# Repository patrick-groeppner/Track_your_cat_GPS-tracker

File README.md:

# Track_your_cat_GPS-tracker
project files for the development of a gps tracker for the offline movement tracking of your beloved home cat. Can also be used for other tracking purposes like car movement recordings or the measurement of walking routs

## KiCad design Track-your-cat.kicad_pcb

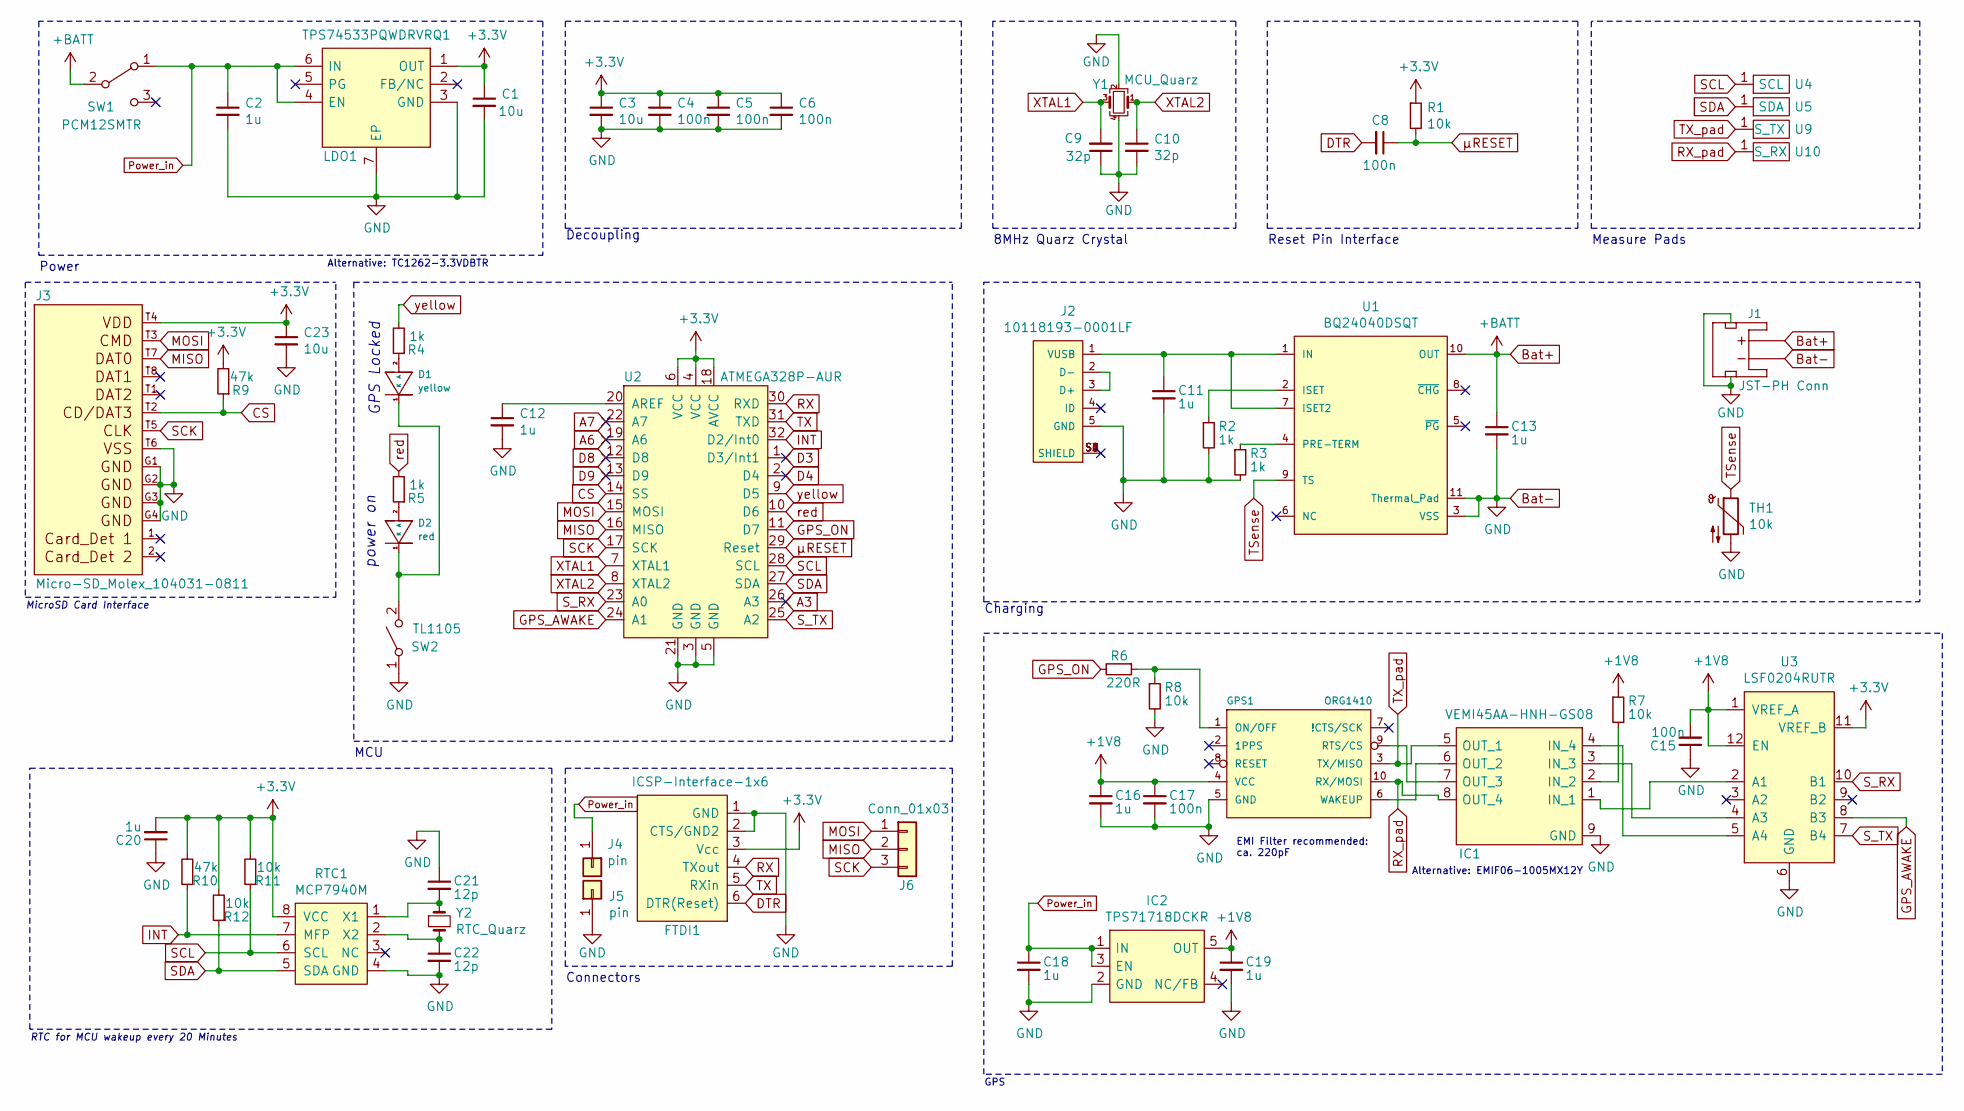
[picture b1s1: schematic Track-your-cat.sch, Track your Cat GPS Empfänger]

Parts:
C1, C3, C23: 10u; C_0805_2012Metric_Pad1.18x1.45mm_HandSolder
C2, C11, C12, C13, C16, C18, C19, C20: 1u; C_0603_1608Metric_Pad1.08x0.95mm_HandSolder
C4, C5, C6, C8, C15, C17: 100n; C_0603_1608Metric_Pad1.08x0.95mm_HandSolder
C9, C10: 32p; C_0603_1608Metric_Pad1.08x0.95mm_HandSolder
C21, C22: 12p; C_0603_1608Metric_Pad1.08x0.95mm_HandSolder
D1: yellow; LED_3MM
D2: red; LED_3MM
FTDI1: ICSP-Interface-1x6; ICSP1; Mouser Part Number ---
GPS1: ORG1410; Mouser Part Number ---
IC1: VEMI45AA-HNH-GS08; Manufacturer_Part_Number VEMI45AA-HNH-GS08; Mouser Part Number 78-VEMI45AA-HNH
IC2: TPS71718DCKR; SC70; Manufacturer_Part_Number TPS71718DCKR; Mouser Part Number 595-TPS71718DCKR
J1: JST_2MM_MALE; JST-2-SMD; Mouser Part Number adafruit 1769
J2: 10118193-0001LF; FCI_10118193-0001LF
J3: Micro-SD_Molex_104031-0811; Micro-SD-Card-Molex_104031-0811; current rating 0.5A; voltage rating 10V; Mouser Part Number 538-104031-0811; digikey description CONN MICRO SD CARD PUSH-PULL R/A
J4, J5: pin; PinHeader_1x01_P2.54mm_Vertical
J6: Conn_01x03; PinHeader_1x03_P2.54mm_Vertical
LDO1: TPS74533PQWDRVRQ1; Manufacturer_Part_Number TPS74533PQWDRVRQ1; Mouser Part Number 595-PS74533PQWDRVRQ1
R1, R7, R8, R11, R12: 10k; R_0603_1608Metric_Pad0.98x0.95mm_HandSolder
R2, R3, R4, R5: 1k; R_0603_1608Metric_Pad0.98x0.95mm_HandSolder
R6: 220R; R_0603_1608Metric_Pad0.98x0.95mm_HandSolder
R9, R10: 47k; R_0603_1608Metric_Pad0.98x0.95mm_HandSolder
RTC1: MCP7940M; SOIC-8_W3.9mm; Mouser Part Nbr. 579-MCP7940MT-I/SN
SW1: PCM12SMTR; Mouser Part Number CUS-13TB PCM12SMTR
SW2: TL1105; TL1105VF250Q
TH1: 10k; THERM_NXRT15XH103FA1B040; Mouser Part Nbr. NXFT15XH103FA2B050
U1: BQ24040DSQT; Texas_Instruments-DSQ0010A-0-0-IPC_C; output voltage 4.2V; Mouser Part Number 595-BQ24040DSQT; digikey description IC BATT CHG LI-ION 1 CELL 10SON
U2: ATMEGA328P-AUR; TQFP-32_7x7mm; MPN ATMEGA328P-AUR; Digi-Key_PN ATMEGA328P-AURCT-ND
U3: LSF0204RUTR; IC_LSF0204RUTR; PARTREV 4210580/C 06/12
U4: SCL; Single0805pad
U5: SDA; Single0805pad
U9: S_TX; Single0805pad
U10: S_RX; Single0805pad
Y1: MCU_Quarz; Crystal_SMD_3225-4Pin_3.2x2.5mm_HandSoldering; Mouser Part Number ABM8AIG-8.000MHZ-1Z-T
Y2: RTC_Quarz; XTAL_ECS-.327-12.5-34QN-TR; Mouser Part Nbr. 732-MC30632.7680KA0R

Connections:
+1V8: C15.2, C16.1, C17.1, C19.1, GPS1.4 (VCC), IC2.5 (OUT), R7.1, U3.1 (VREF_A), U3.12 (EN)
+3V3: C1.1, C3.1, C4.1, C5.1, C6.1, C20.2, C23.1, FTDI1.3 (Vcc), J3.T4, LDO1.1 (OUT), R1.1, R9.2, R10.2, R11.2, R12.2, RTC1.8 (VCC), U2.4 (VCC), U2.6 (VCC), U2.18 (AVCC), U3.11 (VREF_B)
A3: U2.26 (A3)
A6: U2.19 (A6)
A7: U2.22 (A7)
Bat+: C13.1, J1.2 (+), SW1.2 (B), U1.10 (OUT)
Bat-: C1.2, C2.2, C3.2, C4.2, C5.2, C6.2, C9.1, C10.2, C11.2, C12.2, C13.2, C15.1, C16.2, C17.2, C18.2, C19.2, C20.1, C21.1, C22.2, C23.2, FTDI1.1 (GND), FTDI1.2 (CTS/GND2), GPS1.5 (GND), IC1.9 (GND), IC2.2 (GND), J1.1 (-), J1.NC1 (PAD1), J1.NC2 (PAD2), J2.5 (GND), J3.G1, J3.G2, J3.G3, J3.G4, J3.T6, J5.1, LDO1.3 (GND), LDO1.7 (EP), R2.2, R3.2, R8.2, RTC1.4 (GND), SW2.1 (A), TH1.2, U1.3 (VSS), U1.11 (Thermal_Pad), U2.3 (GND), U2.5 (GND), U2.21 (GND), U3.6 (GND), Y1.2, Y1.4
CS: J3.T2, R9.1, U2.14 (SS)
D3: U2.1 (D3/Int1)
D4: U2.2 (D4)
D8: U2.12 (D8)
D9: U2.13 (D9)
DTR: C8.2, FTDI1.6 (DTR(Reset))
GPS_AWAKE: U2.24 (A1), U3.8 (B3)
GPS_ON: R6.2, U2.11 (D7)
INT: R10.1, RTC1.7 (MFP), U2.32 (D2/Int0)
MISO: J3.T7, J6.2, U2.16 (MISO)
MOSI: J3.T3, J6.1, U2.15 (MOSI)
unnamed: C11.1, J2.1 (VUSB), U1.1 (IN), U1.7 (ISET2)
unnamed: C12.1, U2.20 (AREF)
unnamed: C21.2, RTC1.1 (X1), Y2.1
unnamed: C22.1, RTC1.2 (X2), Y2.2
unnamed: D1.1 (K), D2.1 (K), SW2.2 (B)
unnamed: D1.2 (A), R4.1
unnamed: D2.2 (A), R5.1
unnamed: GPS1.1 (ON/OFF), R6.1, R8.1
unnamed: GPS1.6 (WAKEUP), IC1.6 (OUT_2)
unnamed: GPS1.9 (RTS/CS), IC1.7 (OUT_3)
unnamed: IC1.1 (IN_1), U3.2 (A1)
unnamed: IC1.2 (IN_2), R7.2
unnamed: IC1.3 (IN_3), U3.4 (A3)
unnamed: IC1.4 (IN_4), U3.5 (A4)
unnamed: J2.2 (D-), J2.3 (D+)
unnamed: J2.S1 (SHIELD), J2.S2 (SHIELD), J2.S3 (SHIELD), J2.S4 (SHIELD), J2.S5 (SHIELD), J2.S6 (SHIELD)
unnamed: R2.1, U1.2 (ISET)
unnamed: R3.1, U1.4 (PRE-TERM)
Power_in: C2.1, C18.1, IC2.1 (IN), IC2.3 (EN), J4.1, LDO1.4 (EN), LDO1.6 (IN), SW1.1 (A)
RX: FTDI1.4 (TXout), U2.30 (RXD)
RX_pad: GPS1.10 (RX/MOSI), IC1.8 (OUT_4), U10.1
SCK: J3.T5, J6.3, U2.17 (SCK)
SCL: R11.1, RTC1.6 (SCL), U2.28 (SCL), U4.1
SDA: R12.1, RTC1.5 (SDA), U2.27 (SDA), U5.1
S_RX: U2.23 (A0), U3.10 (B1)
S_TX: U2.25 (A2), U3.7 (B4)
TSense: TH1.1, U1.9 (TS)
TX: FTDI1.5 (RXin), U2.31 (TXD)
TX_pad: GPS1.3 (TX/MISO), IC1.5 (OUT_1), U9.1
XTAL1: C9.2, U2.7 (XTAL1), Y1.3
XTAL2: C10.1, U2.8 (XTAL2), Y1.1
red: R5.2, U2.10 (D6)
yellow: R4.2, U2.9 (D5)
µRESET: C8.1, R1.2, U2.29 (Reset)

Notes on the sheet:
Connectors
Power
Decoupling
8MHz Quarz Crystal
Reset Pin Interface
Charging
power on
GPS Locked
MicroSD Card Interface
GPS
MCU
Alternative: EMIF06-1005MX12Y
EMI Filter recommended: ca. 220pF
RTC for MCU wakeup every 20 Minutes
Measure Pads
Alternative: TC1262-3.3VDBTR

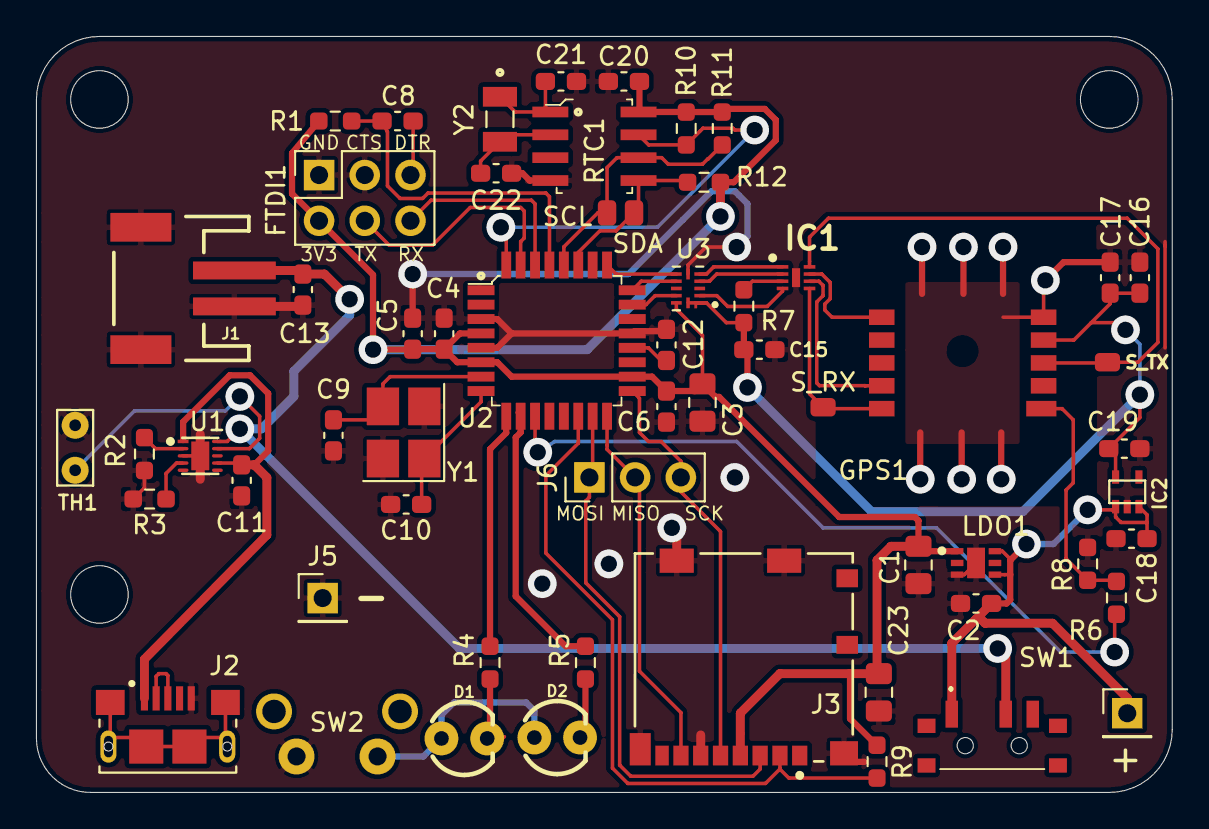
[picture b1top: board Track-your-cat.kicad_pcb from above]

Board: 2 copper layers, 63.1 x 42.0 mm, 62 parts (0 on the bottom side), 45 nets.

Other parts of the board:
H1, H1#2, H1#3: MountingHole_3.2mm_M3

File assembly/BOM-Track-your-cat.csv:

Referenz,Name,Wert,Mouser Teile Nummer,Anzahl,,,,,,,,,,,,,,,,,,,,,,,,,,,,,,,,,,,,,,,,,,,,,,,,,,,,,,,,,,
"    C1, C3, C23",Kondesator,10u,,2,,,,,,,,,,,,,,,,,,,,,,,,,,,,,,,,,,,,,,,,,,,,,,,,,,,,,,,,,,
">  C4-C8, C14, C15, C17",Kondesator,100n,,8,,,,,,,,,,,,,,,,,,,,,,,,,,,,,,,,,,,,,,,,,,,,,,,,,,,,,,,,,,
">  C21, C22",Kondesator,12p,,2,,,,,,,,,,,,,,,,,,,,,,,,,,,,,,,,,,,,,,,,,,,,,,,,,,,,,,,,,,
">  C9, C10",Kondesator,32p,,2,,,,,,,,,,,,,,,,,,,,,,,,,,,,,,,,,,,,,,,,,,,,,,,,,,,,,,,,,,
">  C2, C11-C13, C16, C18-C20",Kondesator,1u,,8,,,,,,,,,,,,,,,,,,,,,,,,,,,,,,,,,,,,,,,,,,,,,,,,,,,,,,,,,,
    D1,LED,yellow,---,1,,,,,,,,,,,,,,,,,,,,,,,,,,,,,,,,,,,,,,,,,,,,,,,,,,,,,,,,,,
    D2,LED,red,---,1,,,,,,,,,,,,,,,,,,,,,,,,,,,,,,,,,,,,,,,,,,,,,,,,,,,,,,,,,,
    FTDI1,Programmer,ICSP-Interface-1x6_female_pins,---,1,,,,,,,,,,,,,,,,,,,,,,,,,,,,,,,,,,,,,,,,,,,,,,,,,,,,,,,,,,
    GPS1,GPS-IC,ORG1410,---,1,,,,,,,,,,,,,,,,,,,,,,,,,,,,,,,,,,,,,,,,,,,,,,,,,,,,,,,,,,
    IC1,EMI Filter,VEMI45AA-HNH-GS08,78-VEMI45AA-HNH,1,,,,,,,,,,,,,,,,,,,,,,,,,,,,,,,,,,,,,,,,,,,,,,,,,,,,,,,,,,1
    IC2,Regulator,TPS71718DCKR,---,1,,,,,,,,,,,,,,,,,,,,,,,,,,,,,,,,,,,,,,,,,,,,,,,,,,,,,,,,,,
    J1,JST-PH Conn,JST-PH 2-pin SMT right angle,adafruit 1769,1,,,,,,,,,,,,,,,,,,,,,,,,,,,,,,,,,,,,,,,,,,,,,,,,,,,,,,,,,,
    J2,Micro USB typ B,USB_B_Micro,Amphenol 10118193-0001LF,1,,,,,,,,,,,,,,,,,,,,,,,,,,,,,,,,,,,,,,,,,,,,,,,,,,,,,,,,,,
    J3,MicroSD Slot,Micro-SD_Molex_104031-0811,538-104031-0811,1,,,,,,,,,,,,,,,,,,,,,,,,,,,,,,,,,,,,,,,,,,,,,,,,,,,,,,,,,,
    LDO1,Regulator,TPS74533PQWDRVRQ1,595-PS74533PQWDRVRQ1,1,,,,,,,,,,,,,,,,,,,,,,,,,,,,,,,,,,,,,,,,,,,,,,,,,,,,,,,,,,
">  R1, R7, R8, R11, R12",Widerstand,10k,,5,,,,,,,,,,,,,,,,,,,,,,,,,,,,,,,,,,,,,,,,,,,,,,,,,,,,,,,,,,
>  R2-R5,Widerstand,1k,,4,,,,,,,,,,,,,,,,,,,,,,,,,,,,,,,,,,,,,,,,,,,,,,,,,,,,,,,,,,
    R6,Widerstand,220R,,1,,,,,,,,,,,,,,,,,,,,,,,,,,,,,,,,,,,,,,,,,,,,,,,,,,,,,,,,,,
">  R9, R10",Widerstand,47k,,2,,,,,,,,,,,,,,,,,,,,,,,,,,,,,,,,,,,,,,,,,,,,,,,,,,,,,,,,,,
    RTC1,RTC,MCP7940M,579-MCP7940MT-I/SN ,1,,,,,,,,,,,,,,,,,,,,,,,,,,,,,,,,,,,,,,,,,,,,,,,,,,,,,,,,,,
    SW1,Schalter,PCM12SMTR,611-PCM12SMTR,1,,,,,,,,,,,,,,,,,,,,,,,,,,,,,,,,,,,,,,,,,,,,,,,,,,,,,,,,,,
    SW2,Schalter,TL1105VF250Q,612-TL1105VF250Q ,1,,,,,,,,,,,,,,,,,,,,,,,,,,,,,,,,,,,,,,,,,,,,,,,,,,,,,,,,,,
    TH1,Thermistor,10k,NXFT15XH103FA2B050 ,1,,,,,,,,,,,,,,,,,,,,,,,,,,,,,,,,,,,,,,,,,,,,,,,,,,,,,,,,,,
    U1,Lade IC,BQ24040DSQT,595-BQ24040DSQT,1,,,,,,,,,,,,,,,,,,,,,,,,,,,,,,,,,,,,,,,,,,,,,,,,,,,,,,,,,,
    U2,MCU,ATMEGA328P-AUR,556-ATMEGA328P-AU,1,,,,,,,,,,,,,,,,,,,,,,,,,,,,,,,,,,,,,,,,,,,,,,,,,,,,,,,,,,
    U3,Logic shifter,LSF0204RUTR,---,1,,,,,,,,,,,,,,,,,,,,,,,,,,,,,,,,,,,,,,,,,,,,,,,,,,,,,,,,,,
    Y1,Crystal,MCU_Quarz,ABM8AIG-8.000MHZ-1Z-T ,1,,,,,,,,,,,,,,,,,,,,,,,,,,,,,,,,,,,,,,,,,,,,,,,,,,,,,,,,,,
    Y2,Crystal,RTC_Quarz,ECS-.327-12.5-34QN-TR ,1,,,,,,,,,,,,,,,,,,,,,,,,,,,,,,,,,,,,,,,,,,,,,,,,,,,,,,,,,,
